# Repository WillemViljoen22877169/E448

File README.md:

# E448

BMS Skripsie:

a Modular battery management system for LFP batteries.

Description:

The project aims to create a Battery Management System (BMS) for sustainable, efficient energy storage, targeting energy sustainability and growing power demands. The scope includes designing a modular, scalable BMS suitable for large LFP battery banks. The approach starts with assessing existing storage technologies and market needs, then designing a flexible, robust system architecture. This BMS will facilitate technological advancements, ensuring relevance in the evolving energy sector.

Clone the repository:

git clone https://github.com/WillemViljoen22877169/E448.git

Contact:

Willem Viljoen
22877169@sun.ac.za

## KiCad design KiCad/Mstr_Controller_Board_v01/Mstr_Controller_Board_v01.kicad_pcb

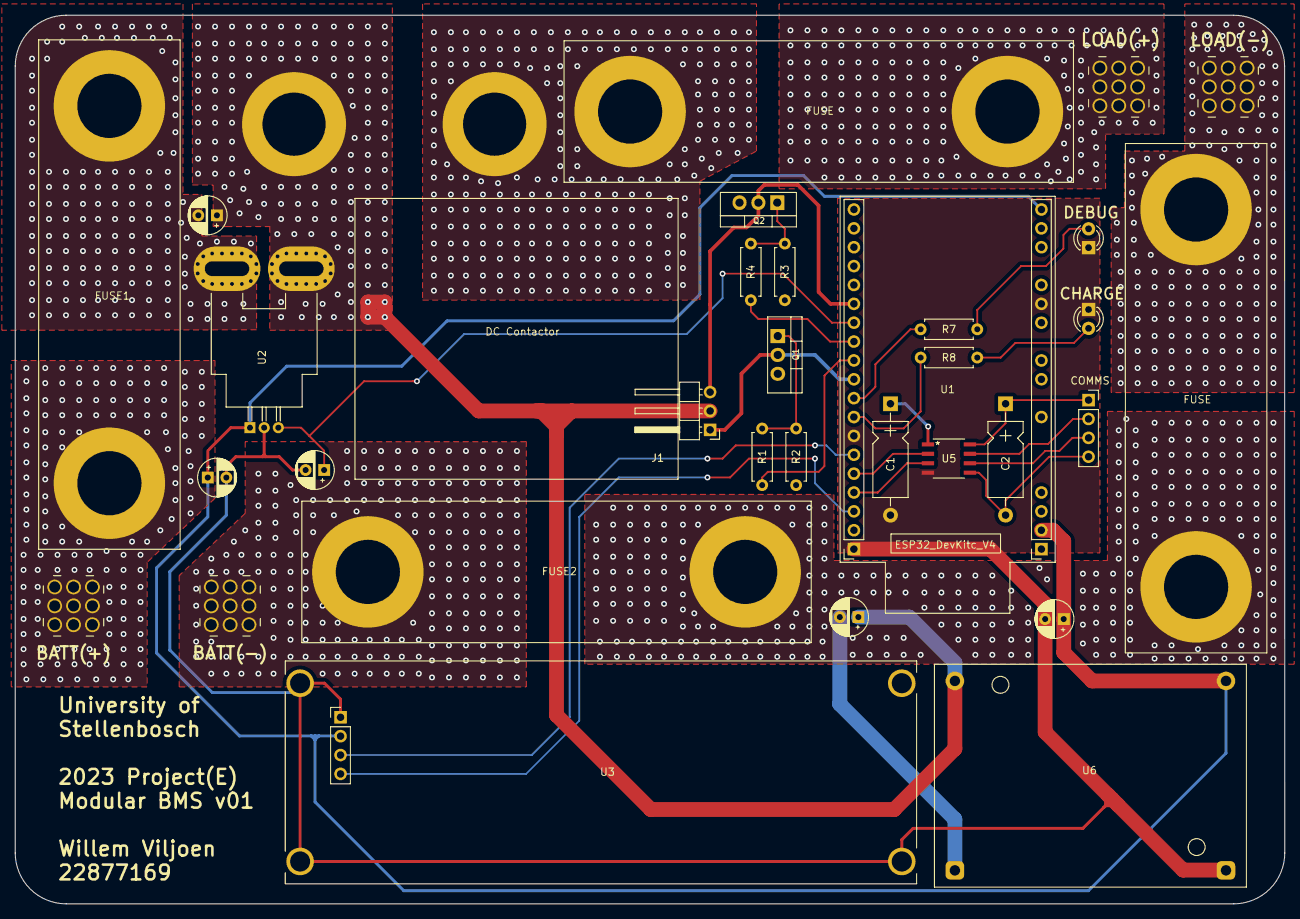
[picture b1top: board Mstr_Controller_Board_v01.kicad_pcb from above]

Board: 2 copper layers, 170.9 x 119.6 mm, 32 parts (0 on the bottom side), 29 nets.

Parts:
C1, C2: 0.1u; CP_Axial_L10.0mm_D4.5mm_P15.00mm_Horizontal
C3, C4, C7: 0.1u; CP_Radial_D5.0mm_P2.50mm
C5, C6: 10n; CP_Radial_D5.0mm_P2.50mm
D1: Debug LED; LED_D3.0mm
D2: Charge ON; LED_D3.0mm
F1, F2, F3, F4: Fuse; BIG_fuse
J1: G9TB-U1ATH-E DC12; PinHeader_1x03_P2.54mm_Horizontal
J2: Comms_ISO_connection; PinSocket_1x04_P2.54mm_Vertical
J3: BATT(+); Wuerth_REDCUBE-THR_WP-THRBU_74650194_THR
J4: BATT(-); Wuerth_REDCUBE-THR_WP-THRBU_74650194_THR
J5: LOAD(+); Wuerth_REDCUBE-THR_WP-THRBU_74650194_THR
J6: LOAD(-); Wuerth_REDCUBE-THR_WP-THRBU_74650194_THR
Q1, Q2: IRF540N; TO-220-3_Vertical
R1, R4: 499; R_Axial_DIN0207_L6.3mm_D2.5mm_P7.62mm_Horizontal
R2, R3: 10k; R_Axial_DIN0207_L6.3mm_D2.5mm_P7.62mm_Horizontal
R7, R8: R; R_Axial_DIN0207_L6.3mm_D2.5mm_P7.62mm_Horizontal
U1: ESP32-DevKitc-V4; MASTERcontroller
U2: ACS770xCB-100B-PFF; Allegro_CB_PFF
U3: LCD_LCM-S01602DSF/C-Y; LCD_LCM-S01602DSF_C-Y
U5: ISO7421D; D8-M
U6: Buck Voltage Regulator; Texas_EUW_R-PDSS-T7_THT

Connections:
/BATT(+): F1.2, J3.1
/BATT(-): F2.2, J4.1
/Comms_ISO_IN: J2.2, U5.7 (INA)
/Comms_ISO_OUT: J2.3, U5.6 (OUTB)
/GND_OFF_Board: C2.2, J2.4, U5.5 (GND2)
/LOAD(+): F3.2, J5.1
/LOAD(-): F4.2, J6.1
/VCC_OFF_Board: C2.1, J2.1, U5.8 (Vcc2)
GND: C1.2, C3.2, C5.2, C7.2, D1.1 (K), D2.1 (K), U1.GND, U2.2 (GND), U3.1, U3.P1, U3.P2, U3.P4, U5.4 (GND1), U6.1 (Vo(-))
I_Sense: C5.1, U1.4, U2.3 (VIOUT)
unnamed: D1.2 (A), R7.1
unnamed: D2.2 (A), R8.1
unnamed: Q1.1 (G), R1.2, R2.1
unnamed: Q2.1 (G), R3.1, R4.2
unnamed: R7.2, U1.18
unnamed: R8.2, U1.19
RX0: U1.RX, U5.2 (OUTA)
SCL: U1.22, U3.4
SDA: U1.21, U3.3
SSS_Reset: R4.1, U1.16
SSS_Set: R1.1, U1.17
TX0: U1.TX, U5.3 (INB)
VCC: C1.1, C3.1, C7.1, U1.5V, U1.EN, U2.1 (VCC), U3.2, U5.1 (Vcc1), U6.2 (Vo(+))
V_Charge/Load(+): F3.1, J1.1
V_batt(+): C4.1, C6.1, J1.2, J1.4, U2.4 (IP+), U6.4 (Vi(+))
V_batt(+)_0: C6.2, F1.1, U2.5 (IP-)
V_batt(-): C4.2, F2.1, F4.1, Q1.3 (S), Q2.3 (S), R2.2, R3.2, U6.3 (Vi(-))
WPU_1: J1.5, Q1.2 (D), U1.5
WPU_2: J1.3, Q2.2 (D), U1.0

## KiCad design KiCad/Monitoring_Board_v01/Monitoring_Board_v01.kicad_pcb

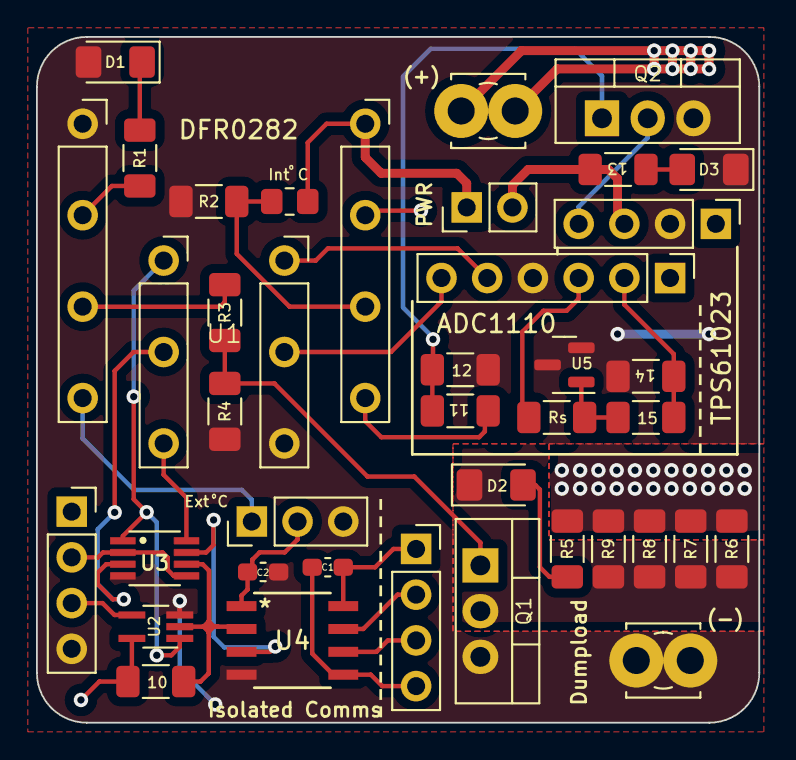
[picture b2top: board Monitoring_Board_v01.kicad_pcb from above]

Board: 2 copper layers, 40.1 x 38.1 mm, 37 parts (0 on the bottom side), 30 nets.

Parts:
C1, C2: C; C_0603_1608Metric_Pad1.08x0.95mm_HandSolder
D1, D2, D3: LED; LED_1206_3216Metric_Pad1.42x1.75mm_HandSolder
J1: ExtTemp_Socket; PinHeader_1x03_P2.54mm_Vertical
J2: 16-bit_ADC; PinHeader_1x06_P2.54mm_Vertical
J3: 5V_Regulator; PinHeader_1x04_P2.54mm_Vertical
J4: Comms_ISO_connection; PinSocket_1x04_P2.54mm_Vertical
J5: Comms_connection; PinSocket_1x04_P2.54mm_Vertical
J6: Supply Jumper; PinHeader_1x02_P2.54mm_Vertical
J7: Cell(+); TerminalBlock_MetzConnect_360272_1x01_Horizontal_ScrewM2.6
J8: Cell(-); TerminalBlock_MetzConnect_360272_1x01_Horizontal_ScrewM2.6
Q1, Q2: IRF540N; TO-220-3_Vertical
R1, R13: 150; R_1206_3216Metric_Pad1.30x1.75mm_HandSolder
R2, R4, R10, R12: 10k; R_1206_3216Metric_Pad1.30x1.75mm_HandSolder
R3, R11: 499; R_1206_3216Metric_Pad1.30x1.75mm_HandSolder
R5: 20; R_1206_3216Metric_Pad1.30x1.75mm_HandSolder
R6, R7, R8, R9: 13; R_1206_3216Metric_Pad1.30x1.75mm_HandSolder
R14, R15: R; R_1206_3216Metric_Pad1.30x1.75mm_HandSolder
Rs1: R; R_1206_3216Metric_Pad1.30x1.75mm_HandSolder
TH1: Thermistor; R_0805_2012Metric_Pad1.20x1.40mm_HandSolder
U1: DFR0282; Arduino_Beetle
U2: 74LVC1G08; SOT-353_SC-70-5_Handsoldering
U3: 74LVC2G08D; TI_ANDgateFP
U4: ISO7421D; D8-M
U5: LM4040DBZ-5; SOT-23

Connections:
/5V_EN: J3.En, Q2.2 (D)
/Comms_IN: J5.2, U3.2 (1B), U3.5 (2A)
/Comms_ISO_IN: J4.2, U4.7 (INA)
/Comms_ISO_OUT: J4.3, U4.6 (OUTB)
/Comms_OUT: J5.3, U2.4 (Y)
/DQ: J1.1, U1.D9
/GND_OFF_Board: C1.2, J4.4, U4.5 (GND2)
/VCC_OFF_Board: C1.1, J4.1, U4.8 (Vcc2)
Dumpload_EN: R3.1, U1.D10
Force_Reset: R11.1, U1.A0
GND1: C2.2, D1.1 (A), D3.1 (K), J1.3, J2.gnd, J3.G, J5.4, J8.1, Q1.3 (S), Q2.3 (S), R2.2, R4.2, R12.2, R14.2, U1.GND1, U2.3 (-), U3.4 (-), U4.4 (GND1), U5.2 (-), U5.3 (NC)
unnamed: D1.2 (K), R1.1
unnamed: D2.2 (A), R5.2
unnamed: D2.1 (K), Q1.2 (D), R6.2, R7.2, R8.2, R9.2
unnamed: D3.2 (A), R13.1
unnamed: J2.Vin-, R14.1, R15.2
unnamed: J2.SCL1, U1.SCL1
unnamed: J2.SDA1, U1.SDA1
unnamed: J3.5Vo, J6.2, R13.2
unnamed: Q1.1 (G), R3.2, R4.1
unnamed: Q2.1 (G), R11.2, R12.1
unnamed: R1.2, U1.D11
unnamed: R2.1, TH1.2, U1.A1
unnamed: R10.2, U2.2 (B), U3.6 (2B), U4.2 (OUTA)
unnamed: U3.7 (1Y), U4.3 (INB)
unnamed: R15.1, Rs1.2, U5.1 (+)
RX0: U1.RX1, U3.3 (2Y)
TX0: U1.TX1, U2.1 (A), U3.1 (1A)
VS: C2.1, J1.2, J2.Vcc, J5.1, J6.1, R10.1, Rs1.1, TH1.1, U1.VCC1, U2.5 (+), U3.8 (+), U4.1 (Vcc1)
V_cell: J2.Vin+, J3.In, J7.1, R5.1, R6.1, R7.1, R8.1, R9.1, U1.A2

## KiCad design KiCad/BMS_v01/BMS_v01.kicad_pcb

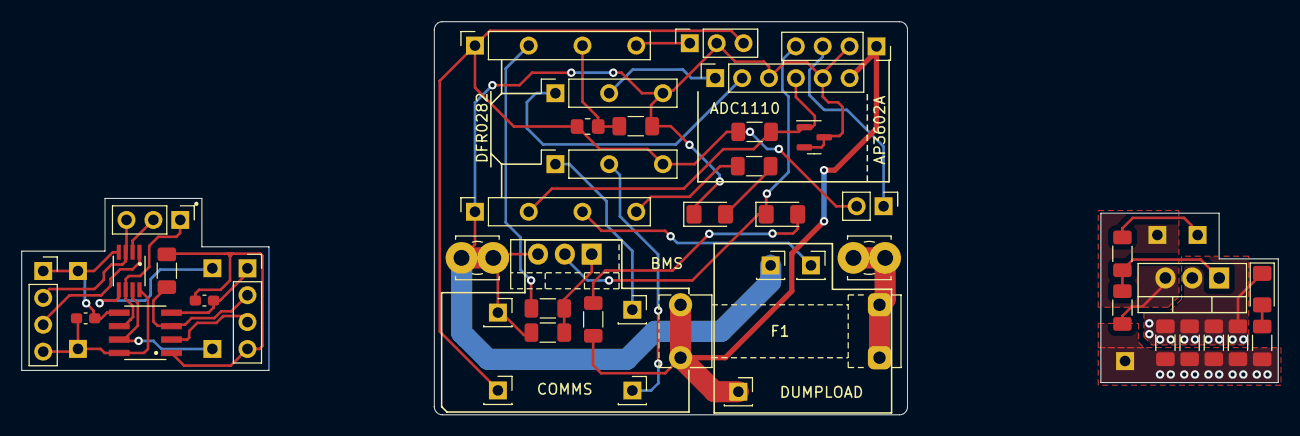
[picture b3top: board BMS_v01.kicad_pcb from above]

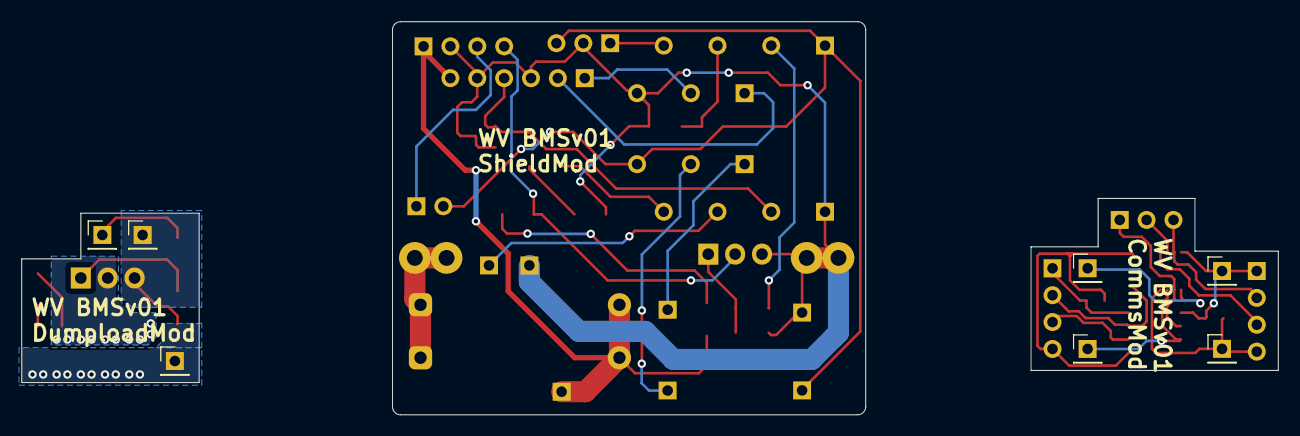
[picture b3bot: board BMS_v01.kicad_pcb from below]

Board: 2 copper layers, 118.7 x 37.1 mm, 53 parts (7 on the bottom side), 32 nets.

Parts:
C1, C2: 0.1u; C_0603_1608Metric_Pad1.08x0.95mm_HandSolder
D1, D2: LED; LED_1206_3216Metric_Pad1.42x1.75mm_HandSolder
D3: Blue LED; LED_1206_3216Metric_Pad1.42x1.75mm_HandSolder
F1: Fuse_Small; Fuseholder_Clip-5x20mm_Littelfuse_111_Lateral_P18.80x5.00mm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
J1, J4: Conn_01x07_Socket; PinSocket_1x07_P2.54mm_Vertical
J2, J3: Conn_01x05_Socket; PinSocket_1x05_P2.54mm_Vertical
J5, J6: Screw_Terminal_01x01; TerminalBlock_MetzConnect_360272_1x01_Horizontal_ScrewM2.6
J7: Conn_01x02_Pin; PinHeader_1x02_P2.54mm_Vertical
J8, J20, J22: Conn_01x04_Socket; PinSocket_1x04_P2.54mm_Vertical
J9, J10, J11, J12, J13, J14, J15: Conn_01x01_Socket; PinSocket_1x01_P2.54mm_Vertical
J16: Conn_01x03_Socket; PinSocket_1x03_P2.54mm_Vertical
J17, J18, J19, J23, J24, J25, J26: Conn_01x01_Pin; PinHeader_1x01_P2.54mm_Vertical
J21: Conn_01x03; PinHeader_1x03_P2.54mm_Vertical
J27: Conn_01x06_Socket; PinSocket_1x06_P2.54mm_Vertical
Q1, Q2: IRF540N; TO-220-3_Vertical
R1, R5: 150; R_1206_3216Metric_Pad1.30x1.75mm_HandSolder
R2, R4, R7, R13: 10k; R_1206_3216Metric_Pad1.30x1.75mm_HandSolder
R3, R6: 499; R_1206_3216Metric_Pad1.30x1.75mm_HandSolder
R8: 20; R_1206_3216Metric_Pad1.30x1.75mm_HandSolder
R9, R10, R11, R12: 13; R_1206_3216Metric_Pad1.30x1.75mm_HandSolder
R14: 10; R_1206_3216Metric_Pad1.30x1.75mm_HandSolder
TH1: Thermistor_NTC_Temp sensor; R_0805_2012Metric_Pad1.20x1.40mm_HandSolder
U1: ISO7421D; ISO7421DchipFP
U2: SN74LVC2G08DCTR; TI_ANDgateFP
U3: LM4040DBZ-5; SOT-23

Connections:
5V: J7.1, J8.3
/A1: J4.3, R2.2, TH1.2
/D9: J1.4, R1.1
C: J21.2, U2.2 (1B)
DQ: J4.4, J16.1
DUMP_LOAD_ENABLE: J1.3, J10.1, J18.1, R6.1
EN(5v): D2.1 (K), J8.4, Q1.2 (D)
GND: D1.1 (K), J1.1, J3.3, J6.1, J8.2, J11.1, J15.1, J16.2, J19.1, J27.3, J27.5, Q1.3 (S), Q2.3 (S), R2.1, R4.2, R7.2, U3.2 (A), U3.3
GND_OFF_Board: C1.1, J20.1, U1.4 (GND1)
GND_ON_Board: C2.2, J22.1, J23.1, U1.5 (GND2), U2.4 (GND)
I2C_scl: J3.1, J27.2
I2C_sda: J3.2, J27.1
INA_OFF_Board: J20.3, U1.2 (OUTA)
INA_ON_Board: J22.3, U2.1 (1A)
unnamed: D1.2 (A), R1.2
unnamed: D2.2 (A), R5.2
unnamed: D3.2 (A), R8.2
unnamed: D3.1 (K), Q2.2 (D), R9.2, R10.2, R11.2, R12.2
unnamed: Q1.1 (G), R3.2, R4.1
unnamed: Q2.1 (G), R6.2, R7.1
OUTB_OFF_Board: J20.2, R13.2, U1.3 (INB)
OUTB_ON_Board: J21.3, J22.2, U2.3 (2Y)
P1: J21.1, U1.6 (OUTB), U2.6 (2B)
RX: J2.2, J12.1, J24.1, U1.7 (INA), U2.7 (1Y)
Reset: J4.2, R3.1
TX: J2.1, J13.1, J25.1, U2.5 (2A)
V_REF: J1.2, J27.4, R14.1, U3.1 (K)
V_batt: F1.2, J8.1, J9.1, J17.1, J27.6, R5.1, R8.1, R9.1, R10.1, R11.1, R12.1
V_terminal: F1.1, J5.1
Vcc_OFF_Board: C1.2, J20.4, R13.1, U1.1 (VCC1)
Vcc_ON_Board: C2.1, J22.4, J26.1, U1.8 (VCC2), U2.8 (VCC)
Vs: J2.3, J4.1, J7.2, J14.1, J16.3, R14.2, TH1.1

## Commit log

2023-03-30 Update README.md
    Start skripsie project tracking.
2023-05-10 Upload KiCad file
    Comms Mod, Dumpload Mod, Shield Mod
2023-05-12 Final preparation.
    Report draft and BOM with datasheets.
2023-06-12 Final PCB
    New PCB layout, new 5v power supply.
2023-06-13 First versions of Arduino code files.
2023-11-09 Skripsie Files
    Workspace for final year project.
